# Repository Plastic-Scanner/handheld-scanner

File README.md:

# A handheld plastic identification tool
A handheld version of the PlasticScanner as a part of a master thesis at DTU

> **Warning**
> This is under development and should not be reproduced before a release is published or if you want do develop it yourself.

## Our mission

We believe that plastic sorting and recycling can be improved. Our handheld Plastic Scanner enhances the process by immediately identifying various plastic types. It can be used in both residential and large waste management settings.

## The handheld Plastic Scanner

A compact handheld Plastic Scanner that contains a small breakout board with ADC, amplifier, LED controller and a color sensor, that can be effortlessly interfaced using the Qwiic/StemmaQT I2C connectors. 

## Changes from the original Plastic Scanner

The board has the following changes from the original:
- The ADC [ADS1256](https://www.ti.com/product/ADS1256) we interfaced SPI is exchanged for the NAU7802 ADC that we interface via I2C
- [AS7341](https://ams.com/as7341) I2C color sensor added
- 5v changed to 3.3v to comply with Qwiic/stemmaQT guidelines

## Notes
- Holes are M2 holes (iso 7380)

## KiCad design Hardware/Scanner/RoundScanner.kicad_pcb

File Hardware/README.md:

> **Warning**
> Documentation under development.

# Electronics hardware
To make the handheld scanner, the hardware is divided into two modules, connected by a JST SH4 cable following the standards of [Sparkfun's Qwiic](https://www.sparkfun.com/qwiic#faqs "Link to the SparkFun QWIIC FAQs") and [Adafruit's StemmaQT](https://learn.adafruit.com/introducing-adafruit-stemma-qt/technical-specs "Link to the Adafruit StemmaQT technical specifications"). 

The handheld scanner will contain of the following modules:
- Scanner module
- Controller module

# Scanner module
The scanner module has has all NIR LEDs, a LED controller to turn the LEDs on and off, an ADC to measure the reflectance and a color sensor to estimate the color of the speciment.

Via the Qwiic/StemmaQT connector, it´s possible to communicate with the color sensor, ADC and LED controller via I2C. The board also has holes for regular pin connections. This means that when your goal is to just perform a scan, you just need to connect any controller to the scanner module

# Controller module
The controller module is intended to control the scanner, handle data, give user feedback and provide power for the whole scanner. 
The board is designed to fit a development-board with the [Adafruit feather layout](https://learn.adafruit.com/adafruit-feather/feather-specification "Link to Sdafruits info on feather design"). 

## Why the Feather layout?
The Adafruit Feather is well specified and openly available on [Adafruit's website](https://learn.adafruit.com/adafruit-feather/feather-specification "Link to Adafruit's info on Feather design") and there is a large variety of boards being designed with the same basic pin-out. This allows other makers to choose the specific microcontroller that fits their needs. 

Feather boards have battery charging capability and management and use 3.3v logic.

Another reason to use a feather layout is to use the well-documented ESP32 board, to minimize problems with missing documentation and avoid pin-out re-arrangement when using different logic boards.

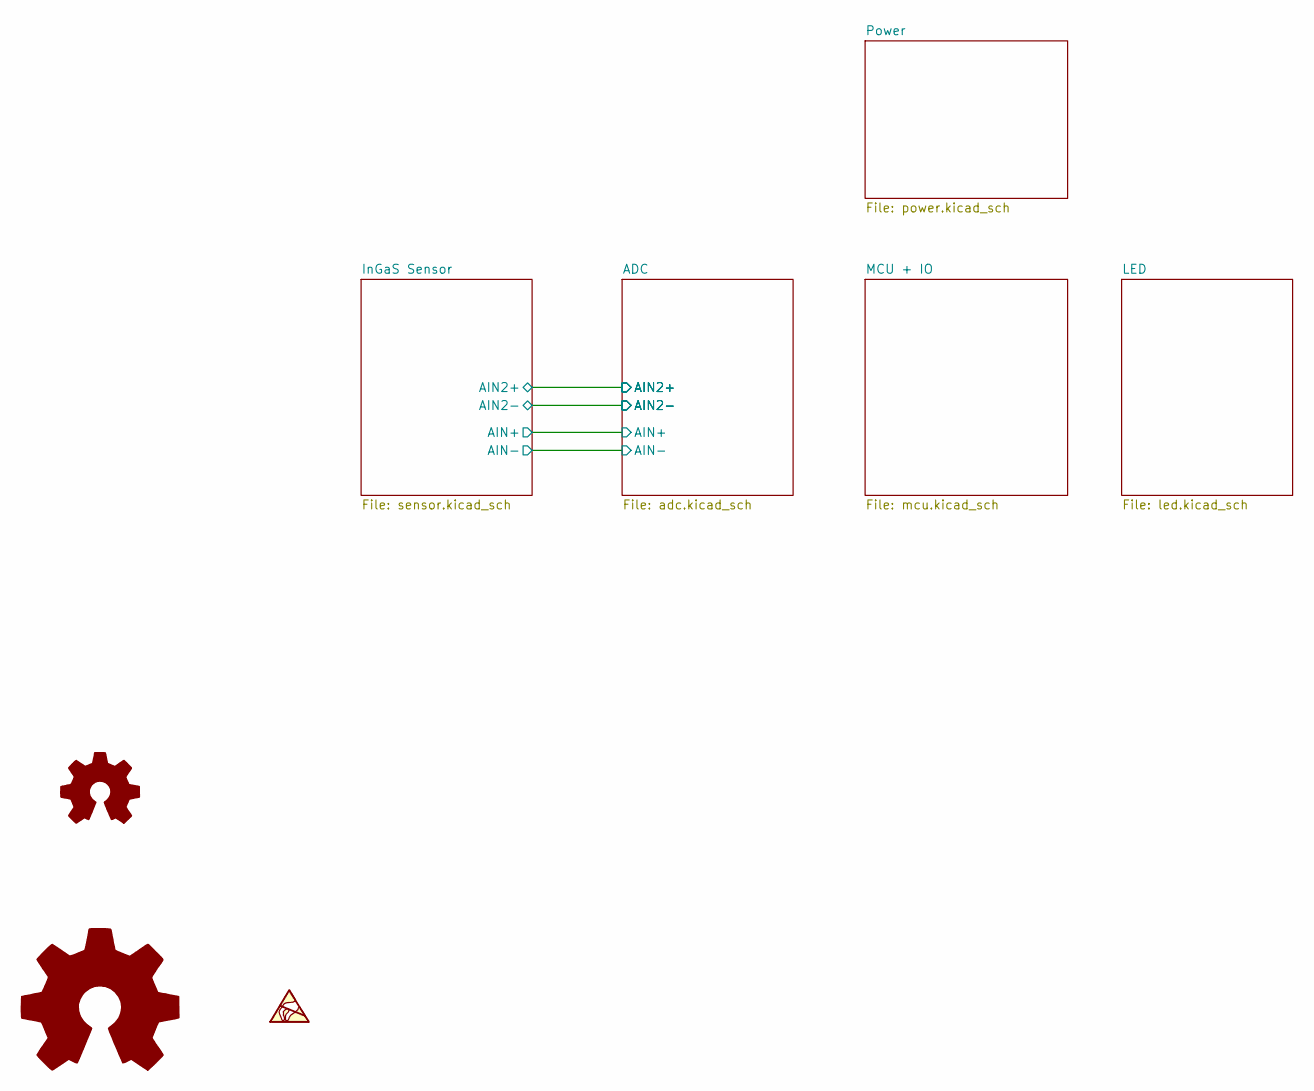
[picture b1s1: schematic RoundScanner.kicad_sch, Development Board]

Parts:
LOGO1: OSHW-Logo_11.4x12mm_SilkScreen
LOGO2: PlasticScannerLogo

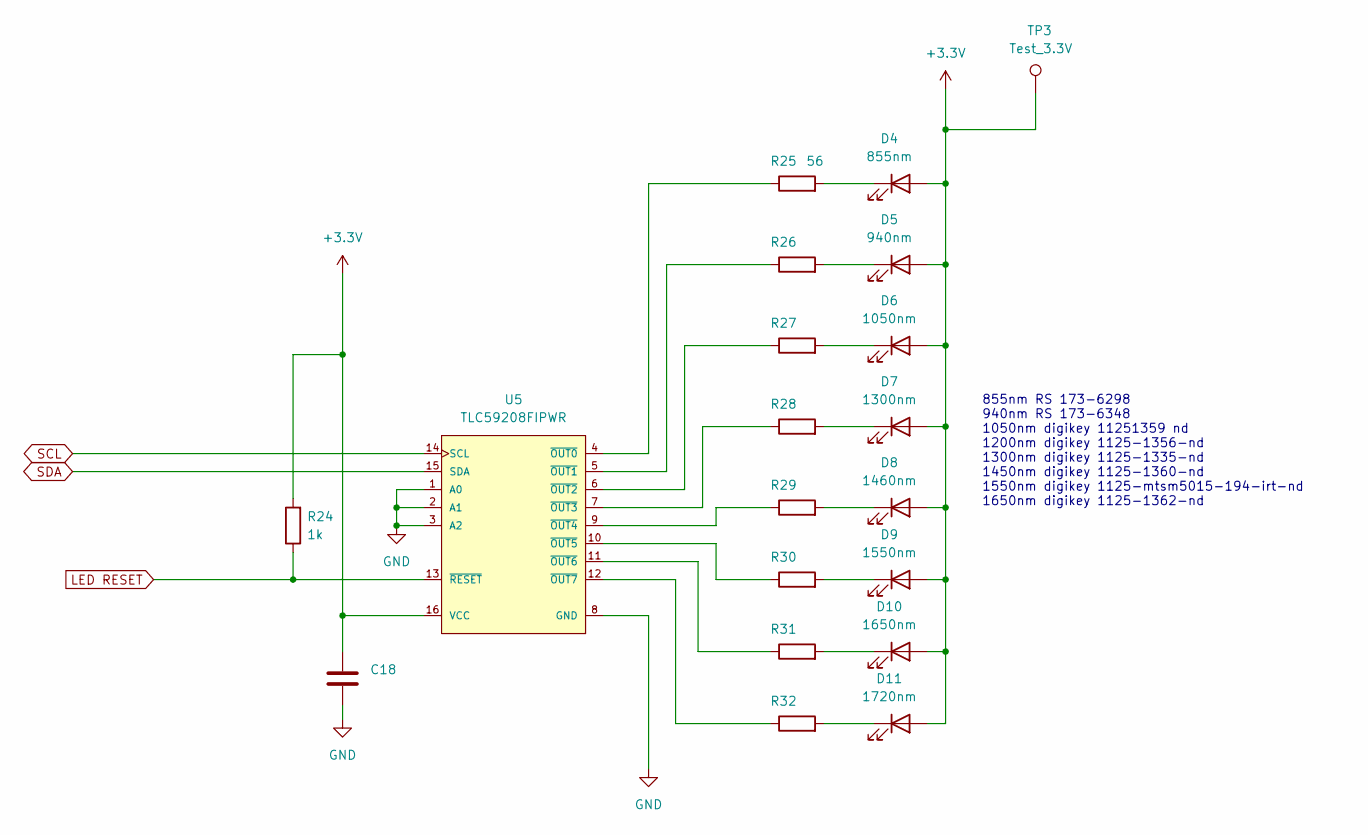
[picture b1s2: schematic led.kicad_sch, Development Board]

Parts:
C18: C_0603_1608Metric_Pad1.08x0.95mm_HandSolder
D4: 855nm; LED_1206_3216Metric_Pad1.42x1.75mm_HandSolder
D5: 940nm; LED_1206_3216Metric_Pad1.42x1.75mm_HandSolder
D6: 1050nm; LED_1206_3216Metric_Pad1.42x1.75mm_HandSolder
D7: 1300nm; LED_1206_3216Metric_Pad1.42x1.75mm_HandSolder
D8: 1460nm; LED_1206_3216Metric_Pad1.42x1.75mm_HandSolder
D9: 1550nm; LED_1206_3216Metric_Pad1.42x1.75mm_HandSolder
D10: 1650nm; LED_1206_3216Metric_Pad1.42x1.75mm_HandSolder
D11: 1720nm; LED_1206_3216Metric_Pad1.42x1.75mm_HandSolder
R24: 1k; R_0603_1608Metric_Pad0.98x0.95mm_HandSolder
R25: 56; R_0603_1608Metric_Pad0.98x0.95mm_HandSolder
R26, R27, R28, R29, R30, R32: R_0603_1608Metric_Pad0.98x0.95mm_HandSolder
R31: (no value)
TP3: Test_3.3V; TestPoint_Pad_D1.5mm
U5: TLC59208FIPWR; SOP65P640X120-16N

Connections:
+3V3: C18.1, D4.2 (A), D5.2 (A), D6.2 (A), D7.2 (A), D8.2 (A), D9.2 (A), D10.2 (A), D11.2 (A), R24.2, TP3.1, U5.16 (VCC); also elsewhere on the board
GND: C18.2, U5.1 (A0), U5.2 (A1), U5.3 (A2), U5.8 (GND); also elsewhere on the board
LED RESET: R24.1, U5.13 (~RESET); also elsewhere on the board
unnamed: D4.1 (K), R25.2
unnamed: D5.1 (K), R26.2
unnamed: D6.1 (K), R27.2
unnamed: D7.1 (K), R28.2
unnamed: D8.1 (K), R29.2
unnamed: D9.1 (K), R30.2
unnamed: D10.1 (K), R31.2
unnamed: D11.1 (K), R32.2
unnamed: R25.1, U5.4 (~OUT0)
unnamed: R26.1, U5.5 (~OUT1)
unnamed: R27.1, U5.6 (~OUT2)
unnamed: R28.1, U5.7 (~OUT3)
unnamed: R29.1, U5.9 (~OUT4)
unnamed: R30.1, U5.10 (~OUT5)
unnamed: R31.1, U5.11 (~OUT6)
unnamed: R32.1, U5.12 (~OUT7)
SCL: U5.14 (SCL); also elsewhere on the board
SDA: U5.15 (SDA); also elsewhere on the board

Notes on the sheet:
855nm RS 173-6298 940nm RS 173-6348 1050nm digikey 11251359 nd 1200nm digikey 1125-1356-nd 1300nm digikey 1125-1335-nd 1450nm digikey 1125-1360-nd 1550nm digikey 1125-mtsm5015-194-irt-nd 1650nm digikey 1125-1362-nd

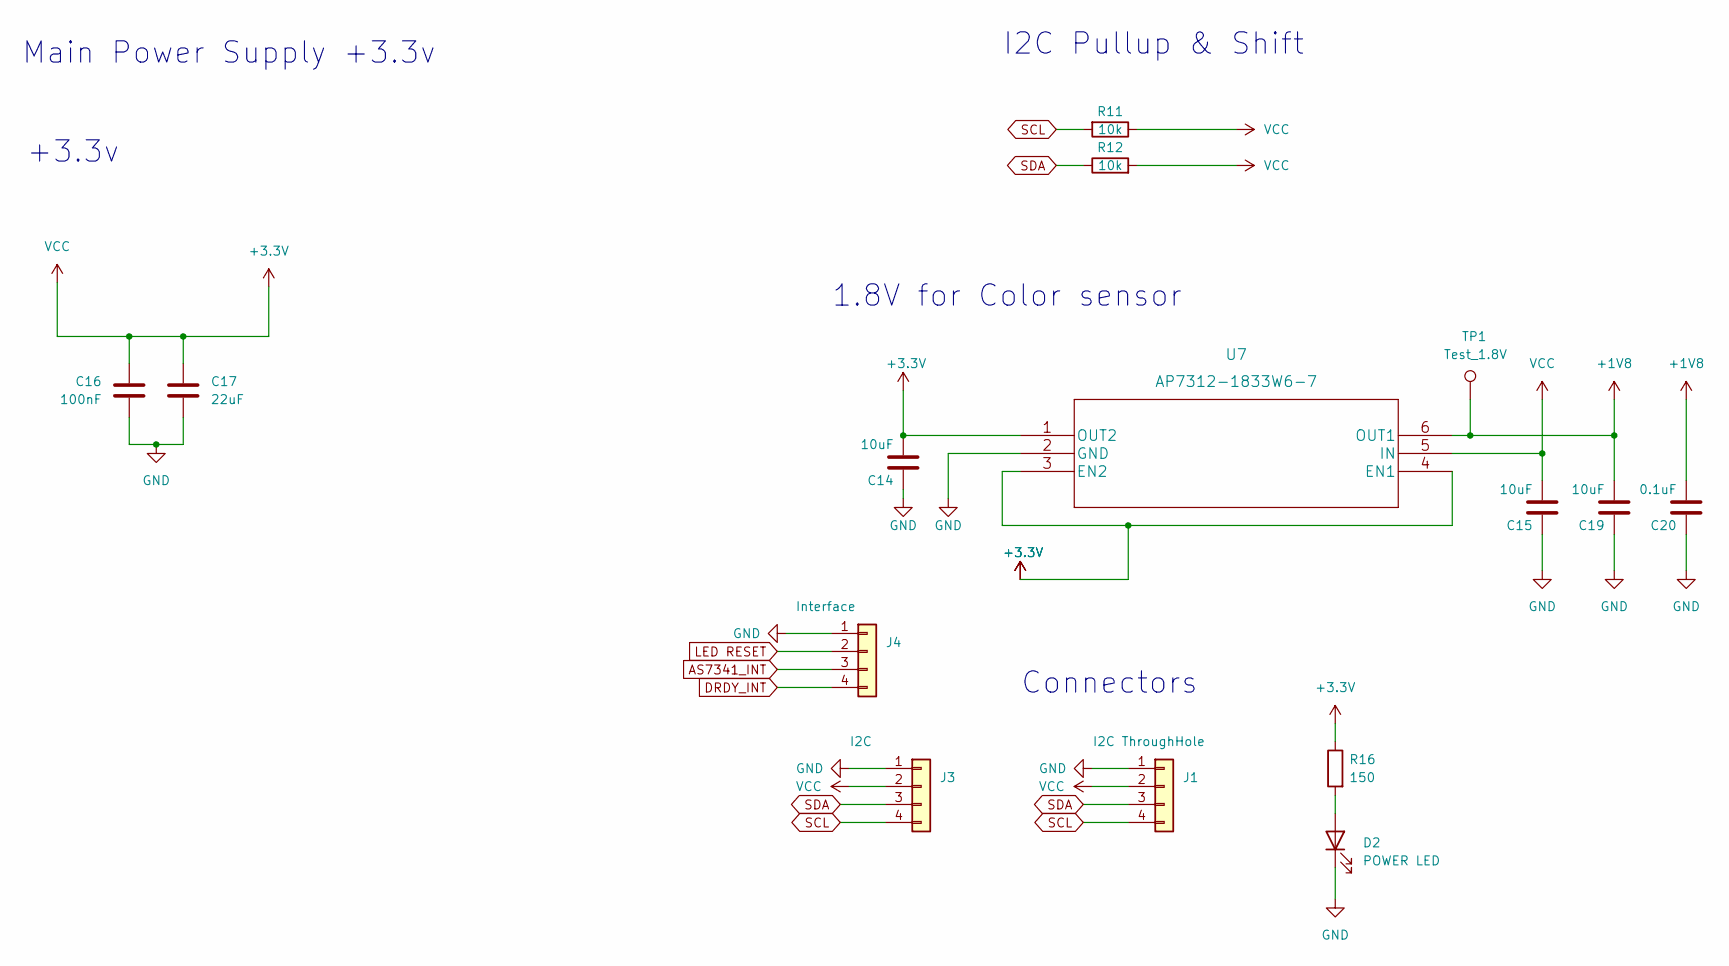
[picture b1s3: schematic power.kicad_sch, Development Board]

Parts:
C14, C15, C19: 10uF; C_0603_1608Metric_Pad1.08x0.95mm_HandSolder
C16: 100nF; C_0603_1608Metric_Pad1.08x0.95mm_HandSolder
C17: 22uF; C_0603_1608Metric_Pad1.08x0.95mm_HandSolder
C20: 0.1uF; C_0603_1608Metric_Pad1.08x0.95mm_HandSolder
D2: POWER LED; LED_0805_2012Metric_Pad1.15x1.40mm_HandSolder
J1: I2C ThroughHole; PinSocket_1x04_P2.54mm_Vertical
J3: I2C; JST_SH_SM04B-SRSS-TB_1x04-1MP_P1.00mm_Horizontal
J4: Interface; PinSocket_1x04_P2.54mm_Vertical
R11, R12: 10k; R_0603_1608Metric_Pad0.98x0.95mm_HandSolder
R16: 150; R_0603_1608Metric_Pad0.98x0.95mm_HandSolder
TP1: Test_1.8V; TestPoint_Pad_D1.5mm
U7: AP7312-1833W6-7

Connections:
+1V8: C19.2, C20.2, TP1.1, U7.6 (OUT1); also elsewhere on the board
+3V3: C14.2, C15.2, C16.2, C17.1, J1.2, J3.2, R11.1, R12.2, R16.1, U7.1 (OUT2), U7.3 (EN2), U7.4 (EN1), U7.5 (IN); also elsewhere on the board
AS7341_INT: J4.3; also elsewhere on the board
DRDY_INT: J4.4; also elsewhere on the board
GND: C14.1, C15.1, C16.1, C17.2, C19.1, C20.1, D2.1 (K), J1.1, J3.1, J4.1, U7.2 (GND); also elsewhere on the board
LED RESET: J4.2; also elsewhere on the board
unnamed: D2.2 (A), R16.2
SCL: J1.4, J3.4, R11.2; also elsewhere on the board
SDA: J1.3, J3.3, R12.1; also elsewhere on the board

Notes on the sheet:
Connectors
Main Power Supply +3.3v
1.8V for Color sensor
+3.3v
I2C Pullup & Shift

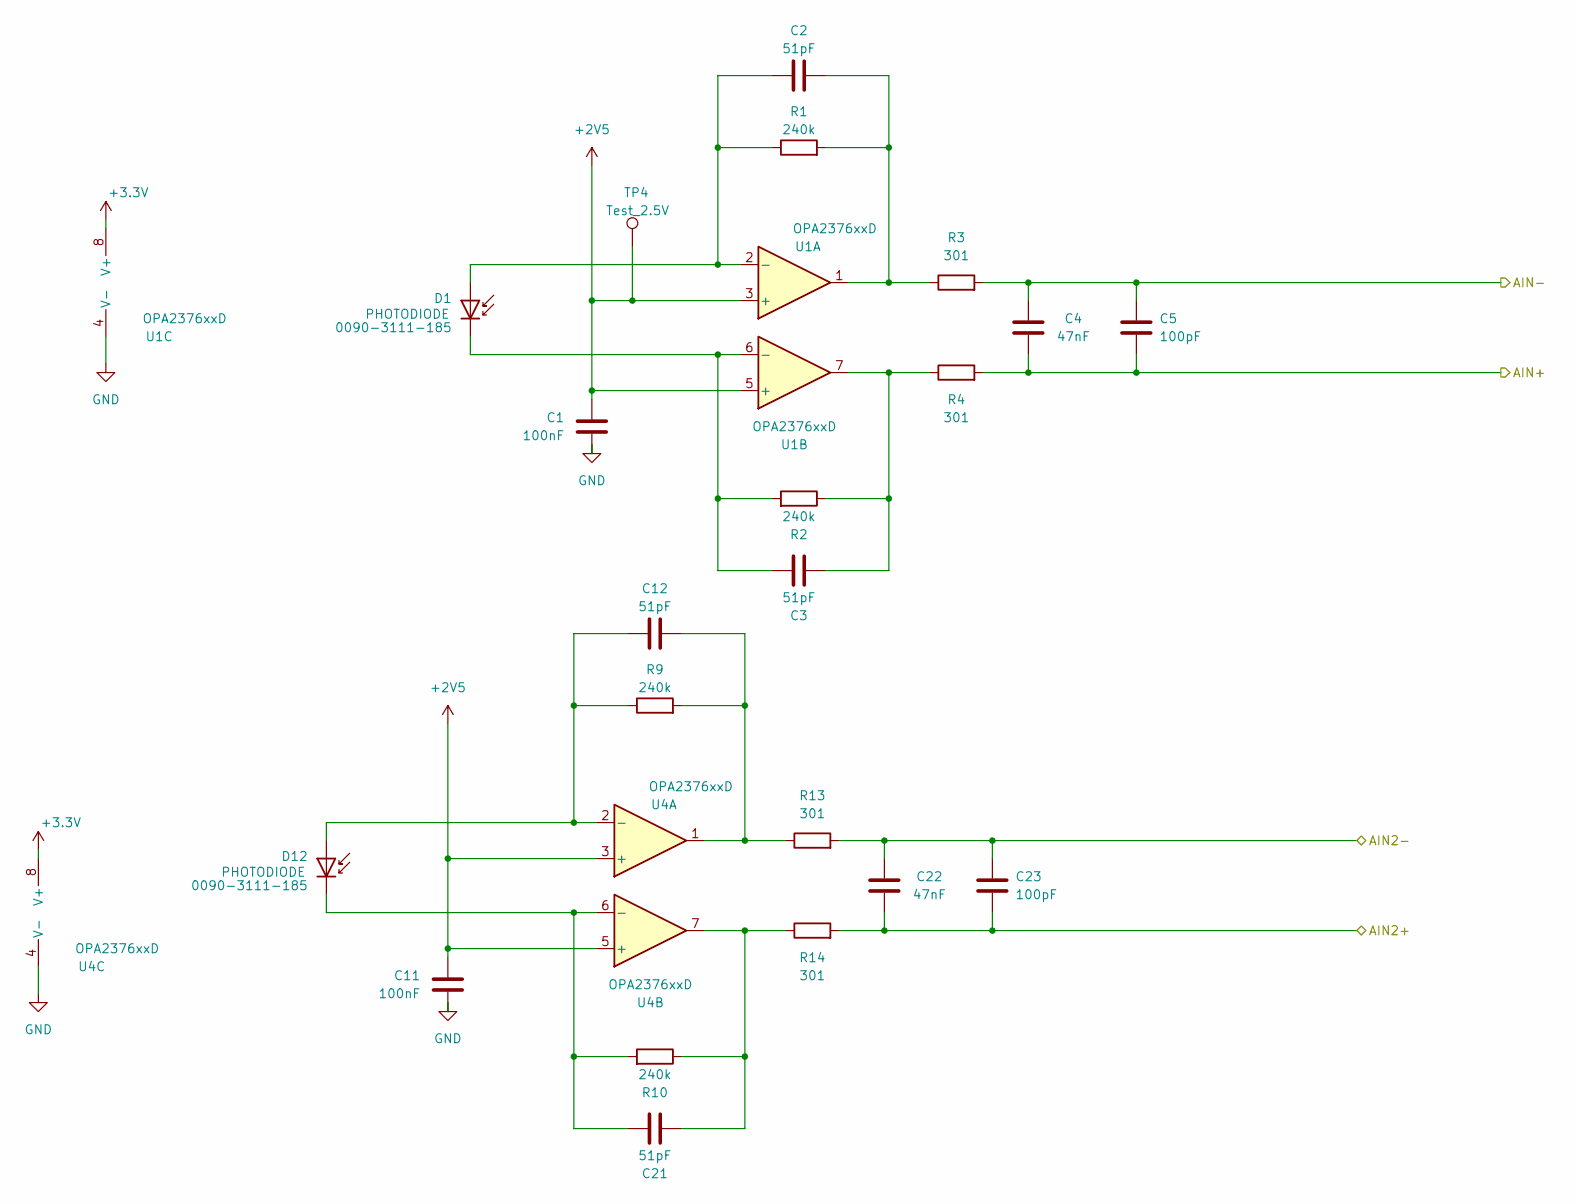
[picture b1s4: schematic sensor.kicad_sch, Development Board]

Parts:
C1, C11: 100nF; C_0603_1608Metric_Pad1.08x0.95mm_HandSolder
C2, C3, C12, C21: 51pF; C_0603_1608Metric_Pad1.08x0.95mm_HandSolder
C4, C22: 47nF; C_0603_1608Metric_Pad1.08x0.95mm_HandSolder
C5, C23: 100pF; C_0603_1608Metric_Pad1.08x0.95mm_HandSolder
D1, D12: 0090-3111-185; D_1206_3216Metric_Pad1.42x1.75mm_HandSolder
R1, R2, R9, R10: 240k; R_0603_1608Metric_Pad0.98x0.95mm_HandSolder
R3, R4, R13, R14: 301; R_0603_1608Metric_Pad0.98x0.95mm_HandSolder
TP4: Test_2.5V; TestPoint_Pad_D1.5mm
U1, U4: OPA2376xxD; SOIC127P599X175-8N

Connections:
+2V5: C1.2, C11.2, TP4.1, U1.3 (+), U1.5 (+), U4.3 (+), U4.5 (+); also elsewhere on the board
+3V3: U1.8 (V+), U4.8 (V+); also elsewhere on the board
/ADC/AIN2+: C22.1, C23.2, R14.2; also elsewhere on the board
/ADC/AIN2-: C22.2, C23.1, R13.2; also elsewhere on the board
/ADC/AIN+: C4.1, C5.2, R4.2; also elsewhere on the board
/ADC/AIN-: C4.2, C5.1, R3.2; also elsewhere on the board
GND: C1.1, C11.1, U1.4 (V-), U4.4 (V-); also elsewhere on the board
unnamed: C2.1, D1.2 (A), R1.1, U1.2 (-)
unnamed: C2.2, R1.2, R3.1, U1.1
unnamed: C3.1, D1.1 (K), R2.2, U1.6 (-)
unnamed: C3.2, R2.1, R4.1, U1.7
unnamed: C12.1, D12.2 (A), R9.1, U4.2 (-)
unnamed: C12.2, R9.2, R13.1, U4.1
unnamed: C21.1, D12.1 (K), R10.2, U4.6 (-)
unnamed: C21.2, R10.1, R14.1, U4.7

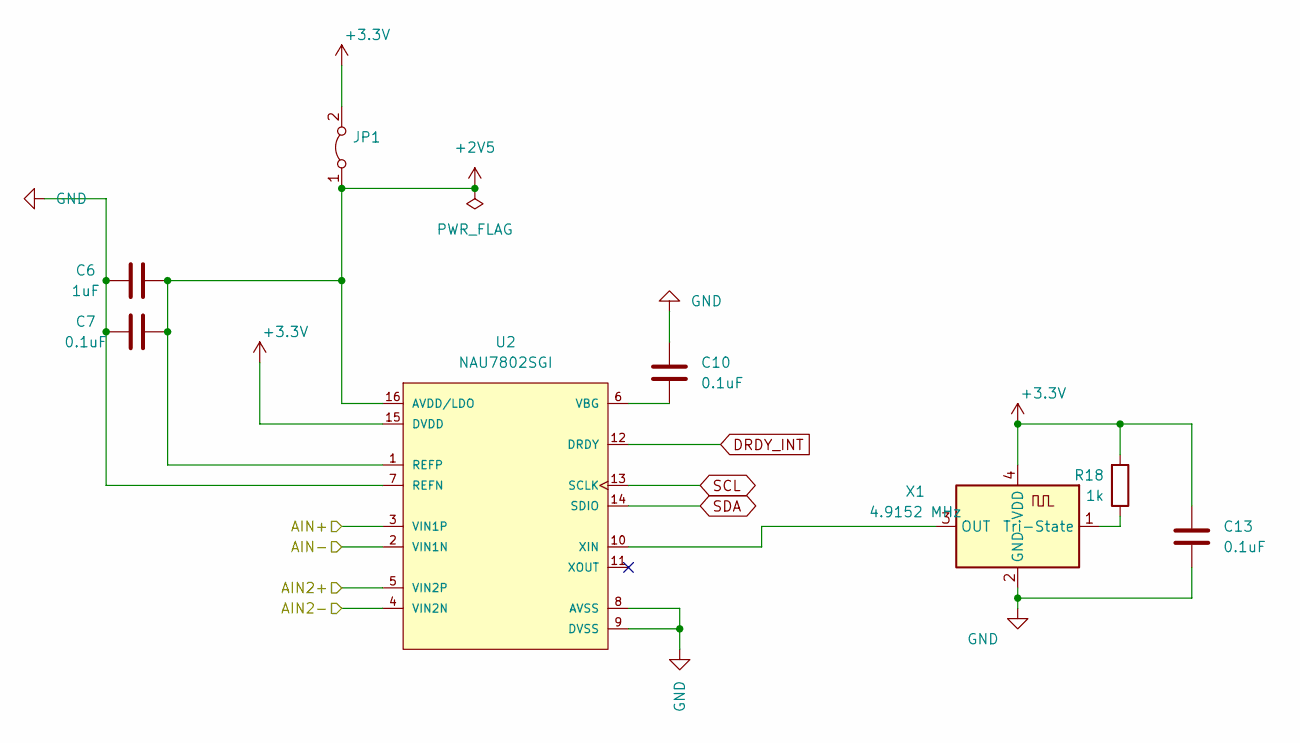
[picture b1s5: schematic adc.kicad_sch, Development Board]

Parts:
C6: 1uF; C_0603_1608Metric_Pad1.08x0.95mm_HandSolder
C7, C10, C13: 0.1uF; C_0603_1608Metric_Pad1.08x0.95mm_HandSolder
JP1: (no value)
R18: 1k; R_0603_1608Metric_Pad0.98x0.95mm_HandSolder
U2: NAU7802SGI; Nuvoton-NAU7802SGI; digikey description IC ADC 24BIT I2C/SRL 16-SOP
X1: 4.9152 MHz; Oscillator_SMD_ECS_2520MV-xxx-xx-4Pin_2.5x2.0mm

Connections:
+2V5: C6.2, C7.2, JP1.1 (A), U2.1 (REFP), U2.16 (AVDD/LDO); also elsewhere on the board
+3V3: C13.1, JP1.2 (B), R18.2, U2.15 (DVDD), X1.4 (VDD); also elsewhere on the board
/ADC/AIN2+: U2.5 (VIN2P); also elsewhere on the board
/ADC/AIN2-: U2.4 (VIN2N); also elsewhere on the board
/ADC/AIN+: U2.3 (VIN1P); also elsewhere on the board
/ADC/AIN-: U2.2 (VIN1N); also elsewhere on the board
DRDY_INT: U2.12 (DRDY); also elsewhere on the board
GND: C6.1, C7.1, C10.1, C13.2, U2.7 (REFN), U2.8 (AVSS), U2.9 (DVSS), X1.2 (GND); also elsewhere on the board
unnamed: C10.2, U2.6 (VBG)
unnamed: R18.1, X1.1 (Tri-State)
unnamed: U2.10 (XIN), X1.3 (OUT)
SCL: U2.13 (SCLK); also elsewhere on the board
SDA: U2.14 (SDIO); also elsewhere on the board

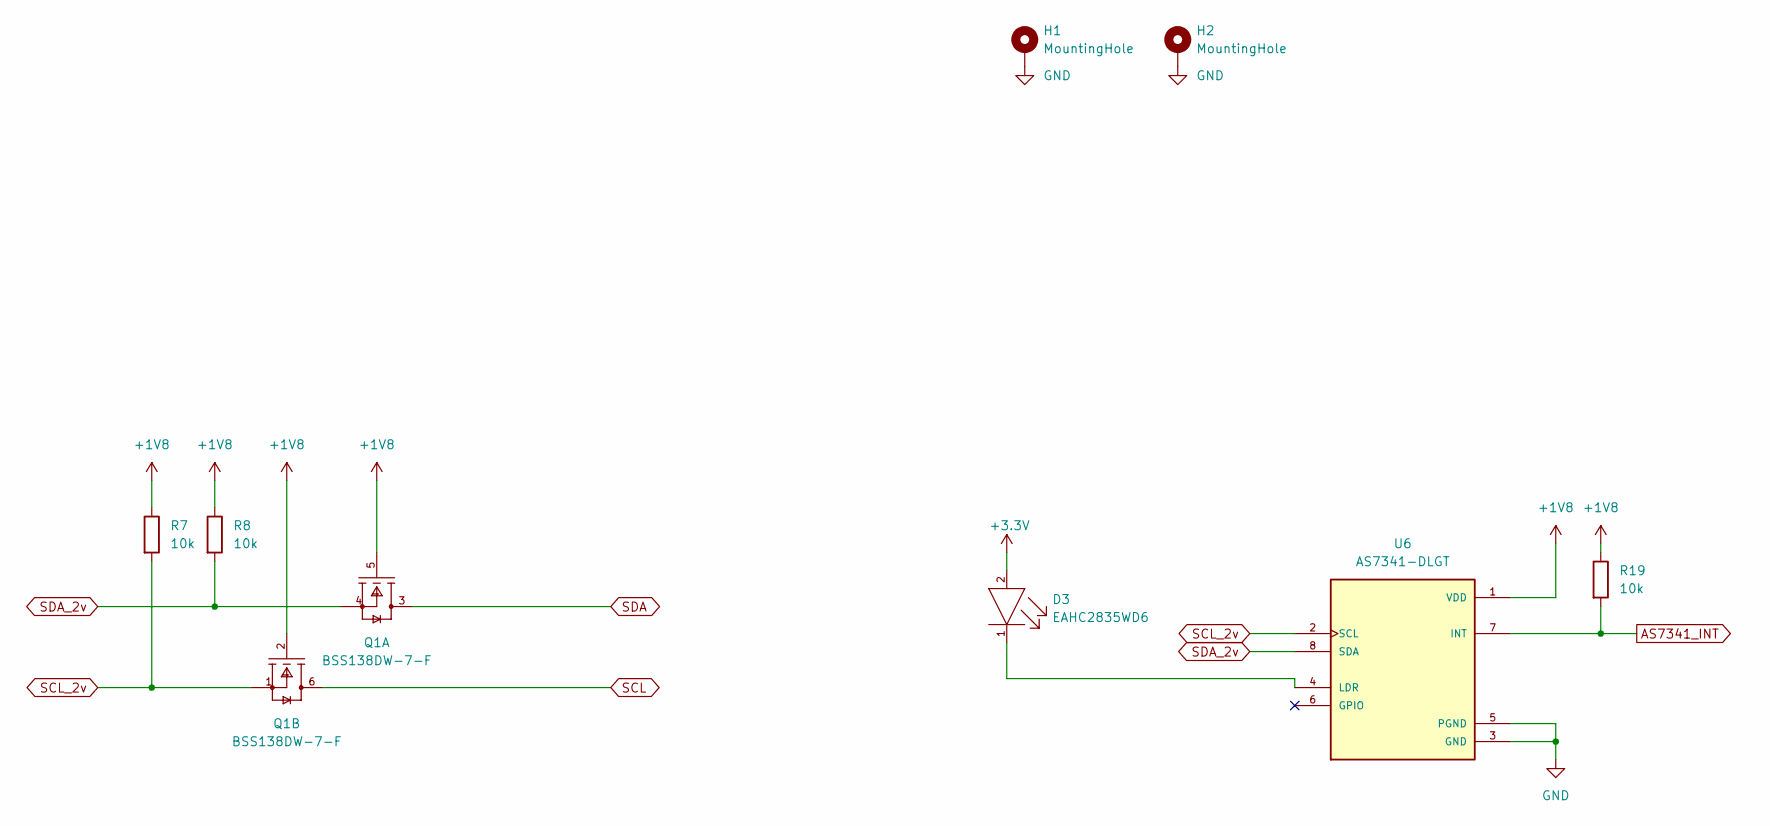
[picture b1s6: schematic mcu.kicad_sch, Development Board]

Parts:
D3: EAHC2835WD6; Everlight-EAHC2835WD6-MFG; forward voltage 3.4V; reverse voltage 5V; mouser part number 638-EAHC2835WD6; digikey description LED COOL WHITE 6500K 2SMD
H1, H2: MountingHole; MountingHole_2.2mm_M2_ISO7380_Pad
Q1: BSS138DW-7-F; Diodes_Inc._-_BSS138DW-7-F-A; mouser part number 621-BSS138DW-F; digikey description MOSFET 2N-CH 50V 0.2A SC70-6
R7, R8, R19: 10k; R_0603_1608Metric_Pad0.98x0.95mm_HandSolder
U6: AS7341-DLGT; PSON80P310X200X110-8N; PARTREV V3

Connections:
+1V8: Q1.2 (G2), Q1.5 (G1), R7.1, R8.1, R19.1, U6.1 (VDD); also elsewhere on the board
+3V3: D3.2 (ANODE); also elsewhere on the board
AS7341_INT: R19.2, U6.7 (INT); also elsewhere on the board
GND: H1.1, H2.1, U6.3 (GND), U6.5 (PGND); also elsewhere on the board
unnamed: D3.1 (CATHODE), U6.4 (LDR)
SCL: Q1.6 (D2); also elsewhere on the board
SCL_2v: Q1.1 (S2), R7.2, U6.2 (SCL)
SDA: Q1.3 (D1); also elsewhere on the board
SDA_2v: Q1.4 (S1), R8.2, U6.8 (SDA)

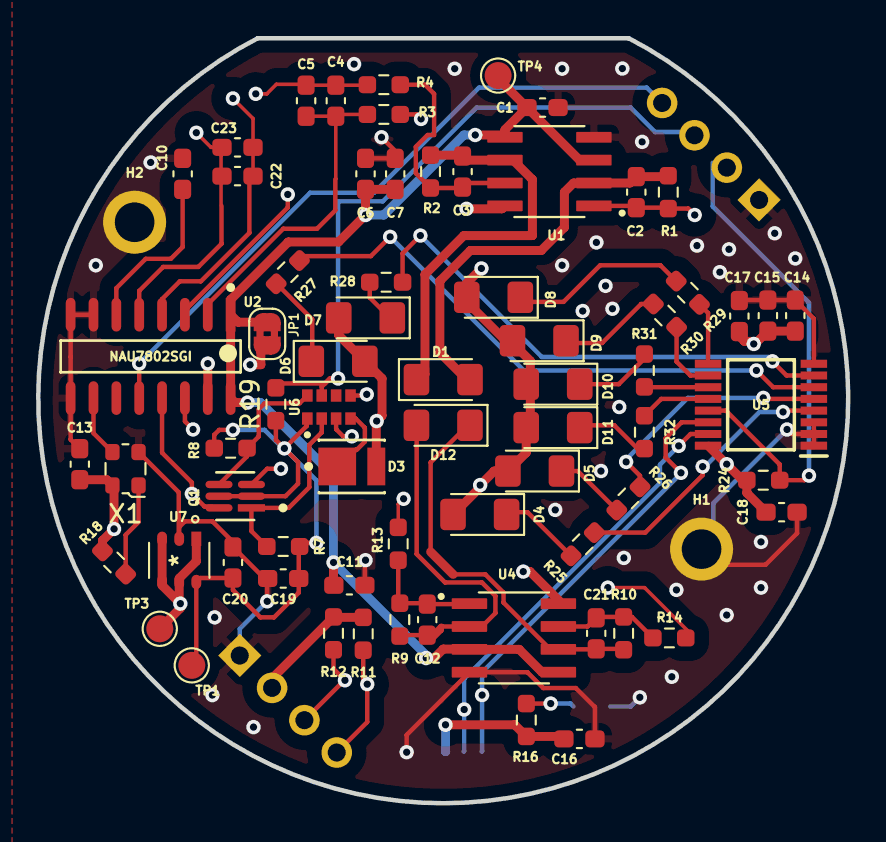
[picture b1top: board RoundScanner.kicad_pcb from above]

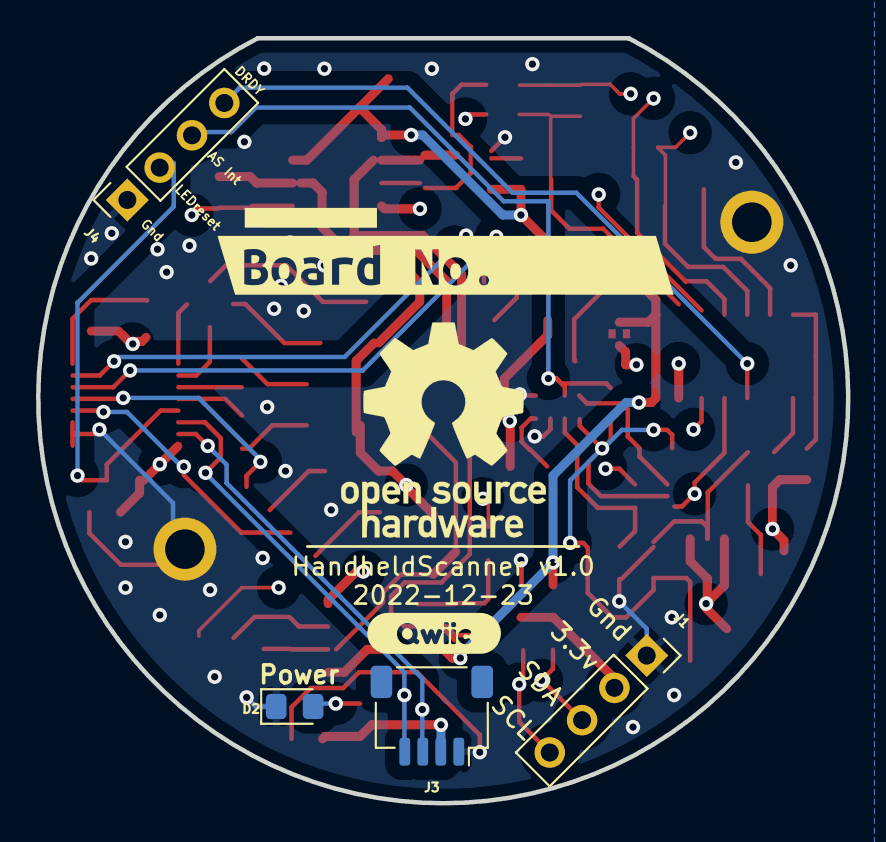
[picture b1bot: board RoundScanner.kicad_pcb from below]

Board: 4 copper layers, 45.0 x 42.5 mm, 78 parts (8 on the bottom side), 44 nets.

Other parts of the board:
kibuzzard-6398DD41: G***; kibuzzard-6398DD41
kibuzzard-6346913B: G***; kibuzzard-6346913B

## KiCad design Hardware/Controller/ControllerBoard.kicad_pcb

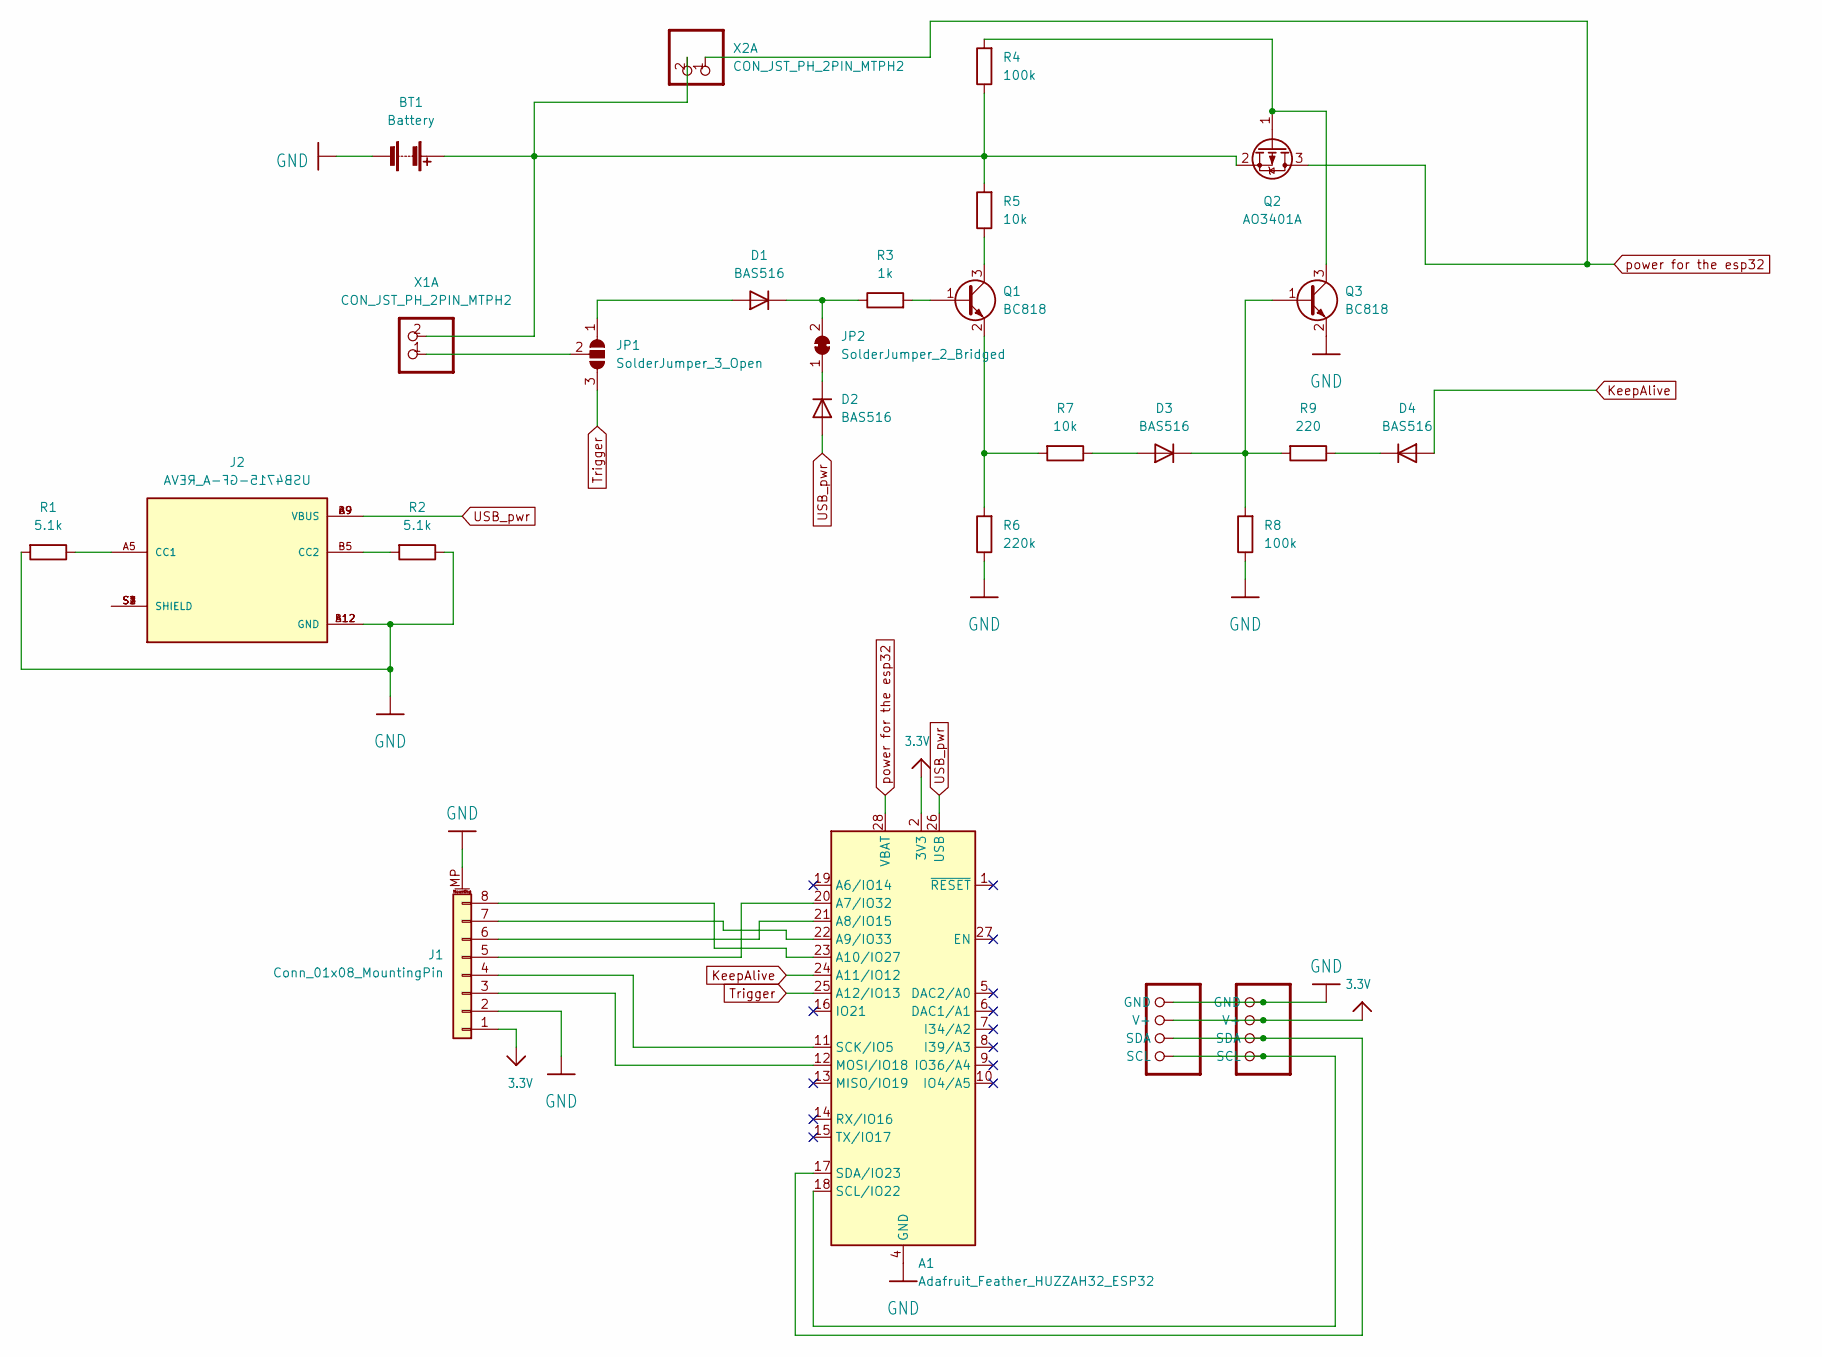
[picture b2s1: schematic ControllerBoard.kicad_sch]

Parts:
A1: Adafruit_Feather_HUZZAH32_ESP32; Adafruit_Feather
BT1: Battery; BatteryHolder_Keystone_2460_1xAA
CONN1, CONN2: STEMMA_I2C_QT; JST_SH_SM04B-SRSS-TB_1x04-1MP_P1.00mm_Horizontal
D1, D2, D3, D4: BAS516; D_SOD-523
J1: Conn_01x08_MountingPin; JST_PH_S8B-PH-SM4-TB_1x08-1MP_P2.00mm_Horizontal
J2: USB4715-GF-A_REVA; GCT_USB4715-GF-A_REVA; PARTREV A
JP1: SolderJumper_3_Open; SolderJumper-3_P1.3mm_Open_Pad1.0x1.5mm_NumberLabels
JP2: SolderJumper_2_Bridged; SolderJumper-2_P1.3mm_Bridged_Pad1.0x1.5mm
Q1, Q3: BC818; SOT-23
Q2: AO3401A; SOT-23
R1, R2: 5.1k; R_0603_1608Metric_Pad0.98x0.95mm_HandSolder
R3: 1k; R_0603_1608Metric_Pad0.98x0.95mm_HandSolder
R4, R8: 100k; R_0603_1608Metric_Pad0.98x0.95mm_HandSolder
R5, R7: 10k; R_0603_1608Metric_Pad0.98x0.95mm_HandSolder
R6: 220k; R_0603_1608Metric_Pad0.98x0.95mm_HandSolder
R9: 220; R_0603_1608Metric_Pad0.98x0.95mm_HandSolder
X1, X2: CON_JST_PH_2PIN_MTPH2; JST_EH_B2B-EH-A_1x02_P2.50mm_Vertical

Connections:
3.3V: A1.2 (3V3), CONN1.2 (V+), CONN2.2 (V+), J1.1
GND: A1.4 (GND), BT1.2 (-), CONN1.1 (GND), CONN2.1 (GND), J1.2, J1.MP (MountPin), J2.A12 (GND), J2.B12 (GND), Q3.2 (E), R1.2, R2.1, R6.1, R8.1
KeepAlive: A1.24 (A11/IO12), D4.2 (A)
unnamed: A1.11 (SCK/IO5), J1.4
unnamed: A1.12 (MOSI/IO18), J1.3
unnamed: A1.17 (SDA/IO23), CONN1.3 (SDA), CONN2.3 (SDA)
unnamed: A1.18 (SCL/IO22), CONN1.4 (SCL), CONN2.4 (SCL)
unnamed: A1.20 (A7/IO32), J1.5
unnamed: A1.21 (A8/IO15), J1.6
unnamed: A1.22 (A9/IO33), J1.7
unnamed: A1.23 (A10/IO27), J1.8
unnamed: BT1.1 (+), Q2.2 (S), R4.1, R5.2, X1.2, X2.2
unnamed: D1.1 (K), JP2.2 (B), R3.1
unnamed: D1.2 (A), JP1.1 (A)
unnamed: D2.1 (K), JP2.1 (A)
unnamed: D3.1 (K), Q3.1 (B), R8.2, R9.2
unnamed: D3.2 (A), R7.1
unnamed: D4.1 (K), R9.1
unnamed: J2.A5 (CC1), R1.1
unnamed: J2.B5 (CC2), R2.2
unnamed: J2.S1 (SHIELD), J2.S2 (SHIELD), J2.S3 (SHIELD), J2.S4 (SHIELD)
unnamed: JP1.2 (C), X1.1
unnamed: Q1.1 (B), R3.2
unnamed: Q1.2 (E), R6.2, R7.2
unnamed: Q1.3 (C), R5.1
unnamed: Q2.1 (G), Q3.3 (C), R4.2
Trigger: A1.25 (A12/IO13), JP1.3 (B)
USB_pwr: A1.26 (USB), D2.2 (A), J2.A9 (VBUS), J2.B9 (VBUS)
power for the esp32: A1.28 (VBAT), Q2.3 (D), X2.1

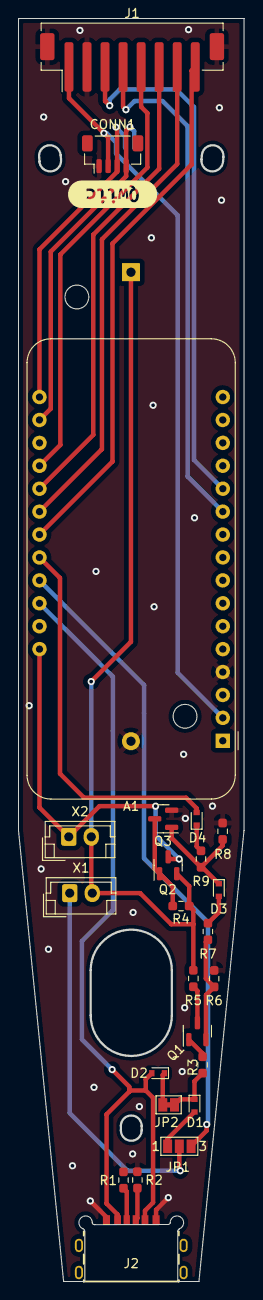
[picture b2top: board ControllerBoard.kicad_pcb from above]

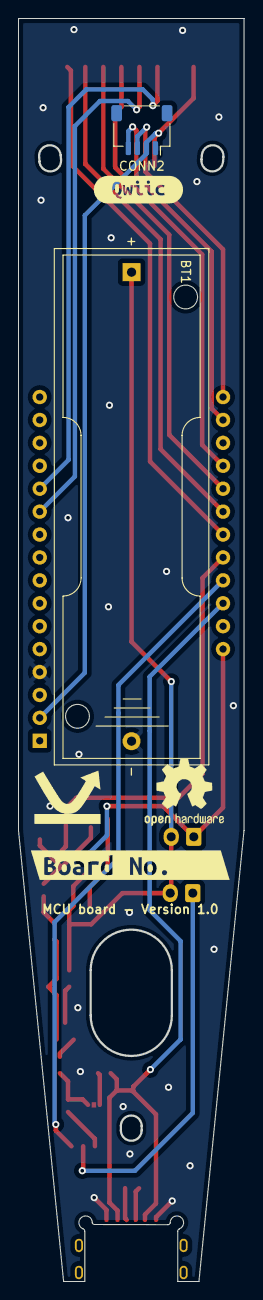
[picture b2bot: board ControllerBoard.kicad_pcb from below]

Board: 2 copper layers, 25.0 x 140.0 mm, 31 parts (6 on the bottom side), 29 nets.

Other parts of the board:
OSH logo: OSHW-Logo2_9.8x8mm_SilkScreen
PlasticScannerLogo: PlasticScannerLogo
kibuzzard-639881D9: G***; kibuzzard-639881D9
kibuzzard-63988507, kibuzzard-63988507#2: G***; kibuzzard-63988507

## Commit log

2022-10-06 New scanner
2022-10-06 hello
2022-10-06 Version 0.1
2022-10-06 Readme updated
2022-10-07 List of changes
2022-10-07 Added gnd zones
2022-10-12 Udated mounting hole layout
2022-10-12 DRC Cleanup
2022-10-12 readme + hole update
2022-10-12 Added ibom
2022-10-12 Added Logos
2022-10-12 Added hole placement measurements
2022-10-15 removed TP561023, added footprint libraries
2022-10-19 Edited 2.5v supply
2022-10-20 Updated power design
2022-10-26 Updated from discord feedback
2022-10-26 Version 0.5
2022-10-30 initial branch commit with rought layout changes
2022-10-31 removed 2.5v circuit to use the built in variable ldo on the ADC added ~4.915Mhz crystal for 50/60Hz filtering fixed several small schematic issues completely relaid out the board.
2022-10-31 added -backups to gitignore lots of layout changes.
2022-11-03 rearranged ir-leds to better optimize path
    most traces routed, evaluating mechanical holes for fitting and optimization
2022-11-07 Updated with changes proposed in dicsord
2022-11-12 in the absence of design docs, I just did my own thing. I've kept the ribbon cable, but I am not sure why there are one on either side, I've also brought out most of the interrupt lines on the throug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
2022-11-29 minor changes
2022-11-29 Version 0.6 - 4 layer version
2022-11-29 Added documentation for production
2022-11-30 removed backup zip files from repo
2022-12-03 optimized layout, cleaned up some traces, opened up the ground and power inner layers so they're less constrained. changed mounting holes to solid to increase ground plane
    verified DRC still passed
2022-12-09 Added pullup resistor to AS7341_INT line
2022-12-13 Qwiic connector fix and removed 3.3v zone in favor of basic routes
2022-12-13 Added MCU PCB
2022-12-13 Added controller board & fixed I2C Qwiic connector
2022-12-13 I2C fix and new text
2022-12-14 battery move and horizontal connector
2022-12-14 Initial mCAD design
2022-12-16 Updated LED and crystal descriptions
2022-12-16 Reestablish 3.3v zone fill on In2.CU
2022-12-19 Consistency of capacitor values
2022-12-19 LED ressistor changes
2022-12-21 LAtching circuit for controller board + minors
2022-12-21 Reroutes tracks to add funtion of latching circuit
2022-12-23 Scanner & Controller Version 1.0
2022-12-23 Added documentation
2023-01-10 First commit - still a small error with compiling
2023-01-10 Update libraries
2023-02-07 Renamed file
    renamed hardware.md to README.md for better visibility on GitHub. Added URLs, fixed some typos.
2023-02-07 Added BHAG and typos fixed
    Added mission and fixed some typos
2023-02-07 Rewritten the mission
    Thanks to chatGPT
2023-02-10 IM Flow simulation
2023-02-10 Move
2023-02-12 Minor updates
2023-02-22 Firmware add
2023-04-13 New 3d files

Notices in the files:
parts and their libraries:
Copyright 2021 Accelerated Designs. All rights reserved.
